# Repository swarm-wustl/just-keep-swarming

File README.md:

# SWARM

# Install

## Pre-Commit Linters

This repository uses a pre-commit hook to validate code quality. First, install the linters with

```
./install_linters.sh
```

Then change the Git hooks path:

```
git config core.hooksPath .githooks
```

Committing changes will now automatically trigger the linting process.

## Gazebo

Gazebo is the physics simulator used by Swarm. The `simulation` package requires that it be installed. To install Gazebo and the bridge for ROS2 Humble, run:

```
sudo apt-get install ros-humble-ros-ign-bridge ros-humble-ros-gz
```

# Build

`cd` into the `ros/` directory, then run:

```
colcon build
```

# Run

For information on how to run packages, see the `README.md` of each package.

## Overhead CV robot tracking README

The overheadCV component of this project can be found in the overhead_cv package

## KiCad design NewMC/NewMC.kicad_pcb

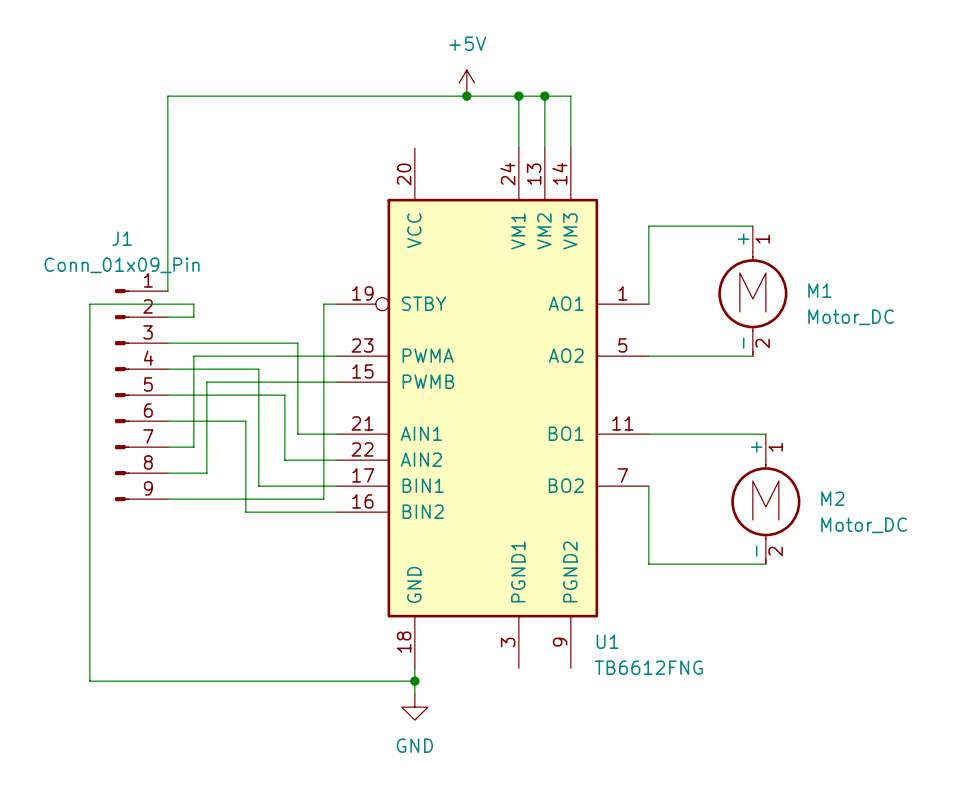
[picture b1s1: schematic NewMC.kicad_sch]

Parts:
J1: Conn_01x09_Pin; esp32
M1, M2: Motor_DC; motor
U1: TB6612FNG; SSOP-24_5.3x8.2mm_P0.65mm

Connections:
+5V: J1.1, U1.13 (VM2), U1.14 (VM3), U1.24 (VM1)
GND: J1.2, U1.18 (GND)
unnamed: J1.3, U1.21 (AIN1)
unnamed: J1.4, U1.17 (BIN1)
unnamed: J1.5, U1.22 (AIN2)
unnamed: J1.6, U1.16 (BIN2)
unnamed: J1.7, U1.23 (PWMA)
unnamed: J1.8, U1.15 (PWMB)
unnamed: J1.9, U1.19 (STBY)
unnamed: M1.1 (+), U1.1 (AO1), U1.2 (AO1)
unnamed: M1.2 (-), U1.5 (AO2), U1.6 (AO2)
unnamed: M2.1 (+), U1.11 (BO1), U1.12 (BO1)
unnamed: M2.2 (-), U1.7 (BO2), U1.8 (BO2)
unnamed: U1.3 (PGND1), U1.4 (PGND1)
unnamed: U1.9 (PGND2), U1.10 (PGND2)

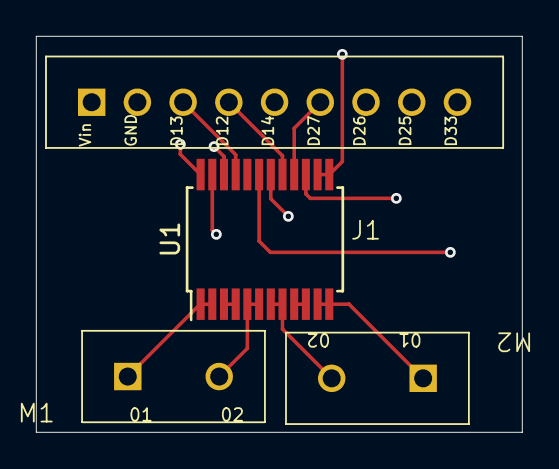
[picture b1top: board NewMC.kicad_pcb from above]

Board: 4 copper layers, 27.0 x 22.0 mm, 4 parts (0 on the bottom side), 15 nets.

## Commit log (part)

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2024-08-03 feat(simulation): added multi-robot simulation
2024-08-03 feat(git): Added pre-commit checks
2024-08-03 test(simulation): Added unit tests for SDF compilation files
2024-08-19 feat(control_algorithms): Implemented A* grid search
2024-08-19 fix(simulation): Linter-inserted xml tag prevented simulation launch
2024-09-10 feat(control_algorithms): Initial S* implementation
2024-09-14 fix(cv2lint): Import cv2 error fixed by pylint disable
2024-09-14 ReadME file to be able to push subfolder
2024-09-14 Update README.txt to include links to components
2024-09-14 fix(installation): Removed colcon from required dependencies for pre-commit linting
2024-09-15 feat(control_algorithms): Implemented prioritized planning algorithm
2024-09-15 test(control_algorithms): Added unit tests for pplan and sstar
2024-09-16 feat(camera_node): Added seperate camera node that publishes to /video topic. Unit tests are also added for overhead_cv
2024-09-16 docs(desc): Updated package description and ReadME
2024-09-16 fix(timer): Changed while loop to timer callback with python
2024-09-16 refactor(submit): Changed submit to use extend
2024-09-16 feat(args): Added args to camera_feed input delay
2024-09-20 fix(installation): Revised pre-commit script
2024-09-21 fix(installation): Added to install_linters_macos.sh so changes take effect without manually restarting terminal
2024-10-04 fix(topic): Fixed topic in map maker
2024-10-11 pixel_to_real ready for testing
2024-10-11 feat(robot_point): Added robot points to og map
2024-10-12 test(map): Added tests for map_maker to test setting and midpoint calculations
2024-10-18 fix(ignore): Removed vscode file
2024-10-18 fix(cam): Fixed cam data troll code
2024-10-18 feat(embedded): Created base ESP-IDF project directory (#5)
    initial starting code
2024-10-18 feat(embedded): Fixed micro-ROS submodule
2024-10-19 feat(control_algorithms): Added algorithms for assembling robots from graph
2024-10-19 Update RaspberryPi
2024-10-19 Patch 3 (#11)
    * ReadME file to be able to push subfolder
    * Update README.txt to include links to components
    * Add files via upload
    * Update README.txt
    * Create RaspberryPi
    * Update RaspberryPi
2024-10-25 fix(git): Added .vscode to .gitignore
2024-10-26 feat(embedded): Created an example with a queue system across tasks
2024-10-26 feat(embedded): Successfully made a subscriber than can receive data
2024-11-01 feat(embedded): Committing submodule changes
2024-11-02 test
2024-11-02 feat(embedded): Successfully transmitted custom messages with uros
2024-11-02 fix(embedded): Added forked uros component, renamed script files
2024-11-02 feat(embedded): Got basic drone data node working, still need to test
2024-11-16 feat(embedded): Controlled motors successfully
2024-11-16 feat(embedded): added direction testing, renamed motor queue push function
2024-11-16 fix(control_algorithms): Improved pplanning algorithm (to some extent)
2024-11-23 refactor(control_algorithms): Refactored obstacle radius inflate
2024-11-23 fix(embedded): Fixed .gitmodules, updated submodule
2024-11-23 feat(embedded): Added PID and PWM controllers, basic implementation of moving to target point
2024-11-25 feat(overhead_cv): Added Kalman filter and frame-to-frame pose tracking (WIP)
2024-11-25 feat(mapping): Created og mapping node utilizing camera feed input and HSV tracking
2024-12-04 fix(embedded): Updated sourcing script to work as intended, added uros dameon script
2024-12-04 feat(embedded): Tested theta and position error calculation. Still need to test on physical hardware
2024-12-06 refactor(embedded): Fixed file structure, separated PID into its own interface
2024-12-06 feat(pylint): Pylint awesomeness
2024-12-06 feat(embedded): Cleaned up drone processing data code
2024-12-06 feat(embedded): Added Kd term to PID controller (untested)
2024-12-07 fix(embedded): Added TODO comment
2024-12-07 feat(dog): Refactor unoptimized code
2024-12-07 feat(awesome): Refactor unoptimized code
2024-12-07 feat(embedded): Rewrote for new drone data
2024-12-07 obstacles added to occupancy grid
2024-12-07 refactor(og): Fixed og_map to use use posearray
2024-12-08 refactor(sub): Fixed some errors specifically with a const function updating a member as I was getting some errors with that
2024-12-08 feat(feedback): Implemented recieving pose array, comparing current and target, and publishing msg
2024-12-08 feat(control): Added integration from mapping to control to robot
2024-12-08 TELEOP
2025-01-18 docs(deprecate): Updated functions that are deprecated
2025-01-18 completely refactored embedded code
2025-01-21 moved some defines from header to source
2025-01-22 motor driver shoulddd be working
2025-01-23 adding the Cadence File to repo
2025-01-23 okay now adding the directory
2025-01-25 replaced test values
2025-01-25 KiCad files (schematic) - dual + normal config
2025-01-25 done
2025-01-25 fixed motors to actually stop
2025-01-25 actually fixed motors stopping
2025-01-25 added TODO
2025-01-29 Add files via upload
    This file include the schematics of the connection between ESP32 and TB6612FNG motor controller see NewMCwESP
    the PCB design for the board carrying TB6612FNG is also included
    For pcb design, JLCPCB 1-2 layer is used
2025-01-29 finished TODOs in motor_driver.c
2025-01-29 feat(folder): Made controller folder
2025-02-01 fix(control_algorithms): Fixed type casting warnings
2025-02-01 started creating PID action server
2025-02-06 got PID action server to build
2025-02-08 buck converter (TPS56637) footprint
2025-02-12 feat(web): Starting code
2025-02-12 refactor(electrical): Move electrical to new repo
2025-02-13 feat(robot_id): Sorted ids by L to R and T to B location and swap after done calibrating. UNTESTED SORTING ALGO LOL (#16)
2025-02-13 working on pid
2025-02-13 fixed weird micro ros thing on this branch
2025-02-13 Planning algorithms (#13)
    * feat(control_algorithms): Add skeleton of control algorithms pkg
    * feat(control_algorithms): Implemented A* grid search
    * feat(control_algorithms): Initial S* implementation
    * feat(overhead): Implemented qr code scanner that gets position and publishes it
    * fix(cv2lint): Import cv2 error fixed by pylint disable
    * feat(control_algorithms): Implemented prioritized planning algorithm
2025-02-15 fix(control_algorithms): Fixed some compilation errors and warnings
2025-02-15 fix(git): Removed .vscode folders
2025-02-19 refactor(shared_types): Combined drone_msg pkg into shared_types pkg
2025-02-19 refactor(overhead_cv): Combined camera_feed into overhead_cv. Made Jaxon's code better
2025-02-19 refactor(overhead_cv): Rewrote cv_recorder -> robot_tracker
2025-02-19 got PID to compile
2025-02-19 added PID TODO
2025-02-19 created ID assign service in assembler_action_server
2025-02-20 fix(position_estimator): Filtered world position was erroneously converted into world pos again
2025-02-22 fix(testing): Removed pytest dependency
2025-02-22 refactor(overhead_cv): Robot_tracker now publishes world positions not pixels; added more type annotations for filtering
2025-02-22 feat(overhead_cv): Added rviz2 to launch file
2025-02-22 fix(position_estimator): Fixed nanoseconds -> seconds conversion
2025-02-22 Refactored overhead_cv and redundant packages (#18)
    * fix(control_algorithms): Fixed some compilation errors and warnings
    * fix(git): Removed .vscode folders
    * refactor(shared_types): Combined drone_msg pkg into shared_types pkg
    * refactor(demo_control): Removed demo control pkg
    * refactor(overhead_cv): Combined camera_feed into overhead_cv. Made Jaxon's code better
    * refactor(overhead_cv): Rewrote cv_recorder -> robot_tracker
2025-02-22 web interface initial setup
2025-03-03 feat(pid_as): Created client creations for control
2025-03-20 feat(pid_as): Implemented integration with position callback for PID control while also modify PID::execute to work correctly
2025-03-22 docs(readme): Working on docs
2025-03-22 fix(predicate): Important fix to movement logic
2025-03-22 angle calculation working
2025-03-22 feat(testing): Begin adding testing clients for pid as
2025-03-22 cleaned up some old code involving memory management
2025-03-26 feat(sevice): Adding initial rob pos service
2025-03-26 working code
2025-03-27 all 4 motors work
2025-03-29 Angle calculation and robot track
2025-03-29 feat(poscallback): PID is able to recieve positiosn and update current position to use in PID algo. PID working is not verified. Also the sim is a bit problematic phyiscs wise
2025-04-02 fixed directions!
2025-04-02 feat(pidas): Testing PID AS lgtm
2025-04-02 all 4 motors working with ros2 messages!
2025-04-05 added comments for future testing
2025-04-05 feat(debug): Adding debug params
2025-04-05 angle_calc
2025-04-07 test(testing): From last testing
2025-04-07 Angle calculation2 (#21)
    * angle calculation working
    * Angle calculation and robot track
    * angle_calc
    * test(testing): From last testing
    ---------
2025-04-07 Fixed Micro-ROS Submodule (#6)
    * feat(embedded): Created base ESP-IDF project directory
    * feat(embedded): Fixed micro-ROS submodule
    * fix(git): Added .vscode to .gitignore
    * feat(embedded): Created an example with a queue system across tasks
    * feat(embedded): Successfully made a subscriber than can receive data
    * feat(embedded): Got custom ROS messages able to be included. Still need to test their functionality
2025-04-07 feat(pub): Added pose pub
2025-04-09 feat(overhead_cv): Attempted to improve filtering and angles
2025-04-14 feat(overhead_cv): Improved angle filtering
2025-04-15 feat(overhead_cv): Wrote EKF, represented theta as sin(theta) cos(theta)
2025-04-16 feat(service): Added robot pos service
2025-04-16 fix(import): Fixing some import errors
2025-04-16 Angle display function in progress
2025-04-26 feat(multi): Multi threaded awesome
2025-04-27 feat(manual_control): Added remote manual control with joystick
2025-04-27 feat(thread): Hopefully thread safe PID
2025-08-12 feat(nix): Add flake.nix
2025-08-12 fix(nix): Update flake.nix to get ROS to build
2025-08-12 feat(nix): Add python packages to flake.nix
2025-09-26 Add gz-cmake
2025-10-01 Service pos control (#23)
    * feat(pub): Added pose pub
    * feat(overhead_cv): Attempted to improve filtering and angles
    * feat(pid): Modified PID to work with one robot
    * feat(overhead_cv): Improved angle filtering
    * feat(overhead_cv): Wrote EKF, represented theta as sin(theta) cos(theta)
    * feat(service): Added robot pos service
2025-10-24 simulation and PID controller working. Implemented Ki, and KD control and fixed robot position issues
2025-11-07 wip(nix): Working on flake for gazebo
2025-11-07 fixed angle movement for PID action server
2025-11-15 created link attacher
2026-02-27 camera_module branch
2026-02-27 placeholder read me with dependencies
2026-02-28 basic preprocessing script; not sure if works yet
2026-03-25 old plan
2026-03-26 Modular sim v0
2026-03-26 Improvements
2026-03-26 Alignment when docking
2026-03-26 Minor fixes
2026-03-27 fixed setup.py
2026-03-30 Abstract docking logic into API
2026-04-03 fixed imu
